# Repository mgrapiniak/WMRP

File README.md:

# Hardware and Arduino Code for DIY WMRP-Solder Station
This is an attempt to implement some improvements:

* Replace LCD with 1.8 Inch Serial SPI TFT LCD Display Module
* Add SPI header onto PCB
* Code amendments

Contributors:
- Bartosz Wapniewski

Video: https://www.youtube.com/watch?v=le2HaKJ6B1A

If you have any questions, please feel free to contact me: flyglas (at) gmail (dot) com

__Features:__
* low offset op amp for soldering tip temperature measurement with type D thermocouple
* cold junction compensation using the PTC (KTY82-110) included in the WMRP soldering pencil
* input voltage measurement (for use with 3 cell lipo battery)
* soldering pencil current measurement 
* recognizing if the soldering pencil rests in the stand (--> standby)
* 3 buttons for save and recall temperature values
* rotary encoder to set soldering temperature
* illuminated 16x2 character LCD module
* USB for debugging and firmware update
* clean and small enclosure
* 4mm safety socket for +12V power input and a protective earth socket for connection to ESD protection

The BOM in the layout folder includes only the parts on the PCB(s).

__Parts (not on PCB):__
* lcd display from ebay "Blue I2C 1602"
* modified connector "Amphenol T 3437 000" (--> http://www.mikrocontroller.net/topic/143288#1500819)
* 4mm safety sockets (red, black, green/yellow) or any other suitable connector
* rotary encoder knob
* display frame "EA027-2UKE"
* aluminium enclosure "Proma 131020"

__Info:__
* close jumper JP1 (activates pullup resistors for I2C wires)
* close jumper JP3 (connection between power ground and analog ground)
* leave jumper JP2 open (alternative for JP3)

__Photos:__

The PCB is a little bit dirty. The Isopropanol was empty and now everything is in the enclosure.

Stand for enclosure Proma 131020:

__First picture of a replica:__

Thank you Dennis for the nice conversation and the picture.

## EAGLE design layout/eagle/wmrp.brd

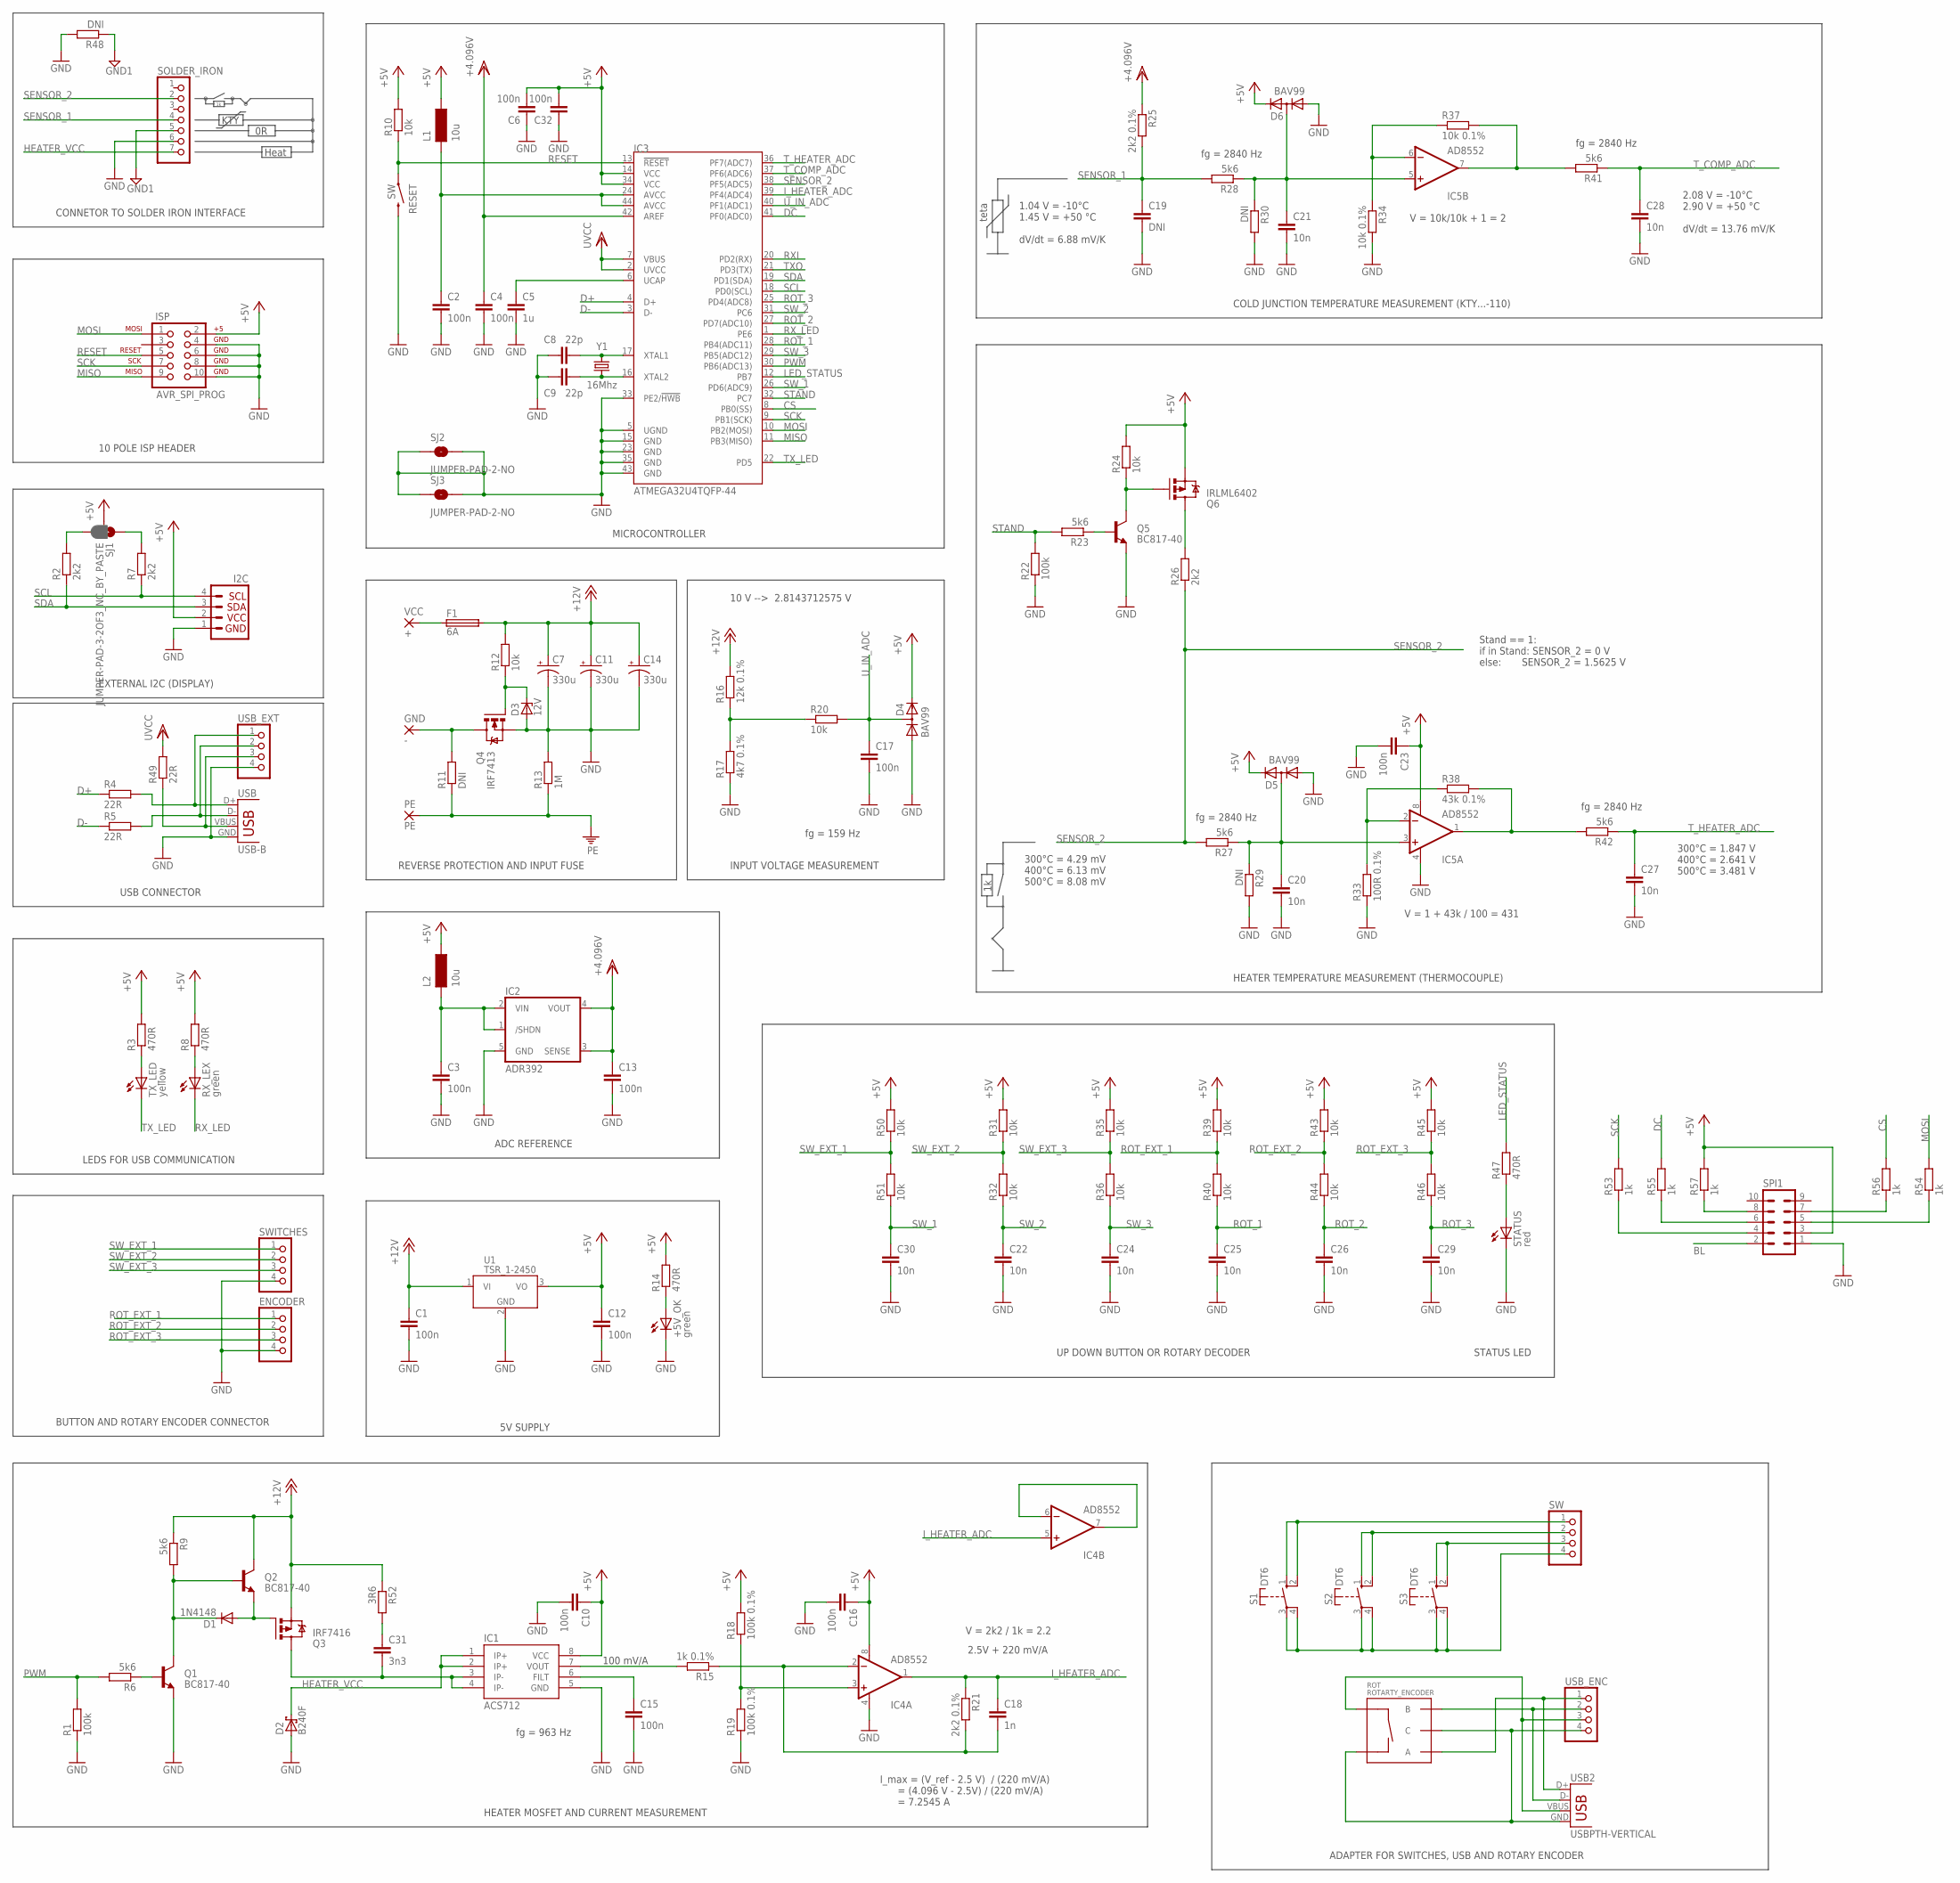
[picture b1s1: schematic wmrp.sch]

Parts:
+5V_OK: green; CHIPLED_1206
C1, C2, C3, C4, C6, C10, C12, C13, C15, C16, C17, C23, C32: 100n; C1206
C5: 1u; C1206
C7, C11, C14: 330u; CPOL-RADIAL-1000UF-25V
C8, C9: 22p; C1206
C18: 1n; C1206
C19: DNI; C1206
C20, C21, C22, C24, C25, C26, C27, C28, C29, C30: 10n; C1206
C31: 3n3; C1206
D1: 1N4148; MINIMELF
D2: B240F; SMB
D3: 12V; SOT23
D4, D5, D6: BAV99; SOT23
ENCODER: PINHD-1X4; 1X04
F1: 6A; SH22,5
GND: -; 2,2
I2C: I2C_STANDARD; 1X04
IC1: ACS712; SO08
IC2: ADR392; SOT23-5
IC3: ATMEGA32U4TQFP-44; TQFP44
IC4, IC5: AD8552; SO08
ISP: AVR_SPI_PROG; AVR_ICSP
L1, L2: 10u; INDUCTOR-1206
PE: PE; 2,2
Q1, Q2, Q5: BC817-40; SOT23-3
Q3: IRF7416; SO-08
Q4: IRF7413; SO-08
Q6: IRLML6402; SOT23-3
R1, R22: 100k; R1206
R2, R7, R26: 2k2; R1206
R3, R8, R14, R47: 470R; R1206
R4, R5, R49: 22R; R1206
R6, R9, R23, R27, R28, R41, R42: 5k6; M1206
R10, R12, R20, R24, R31, R32, R35, R36, R39, R40, R43, R44, R45, R46, R50, R51: 10k; R1206
R11, R48: DNI; R1206
R13: 1M; R1206
R15: 1k 0.1%; M1206
R16: 12k 0.1%; R1206
R17: 4k7 0.1%; R1206
R18, R19: 100k 0.1%; M1206
R21, R25: 2k2 0.1%; M1206
R29, R30: DNI; M1206
R33: 100R 0.1%; M1206
R34, R37: 10k 0.1%; M1206
R38: 43k 0.1%; M1206
R52: 3R6; M1206
R53, R54, R55, R56, R57: 1k; R1206
RESET: SW; TACTILE-PTH
ROT: ROTARTY_ENCODER; ROTARY_ENC_PLAIN
RX_LEX: green; CHIPLED_1206
S1, S2, S3: DT6
SJ1: JUMPER-PAD-3-2OF3_NC_BY_PASTE; PAD-JUMPER-3-2OF3_NC_BY_PASTE_YES_SILK_FULL_BOX
SJ2, SJ3: JUMPER-PAD-2-NO; PAD-JUMPER-2-NO_NO_SILK
SOLDER_IRON: PINHD-1X7; 1X07
SPI1: MA05-2
STATUS: red; CHIPLED_1206
SW: PINHD-1X4; 1X04
SWITCHES: PINHD-1X4; 1X04
TX_LED: yellow; CHIPLED_1206
U1: TSR_1-2450; TSR-1
USB: USB-B; USB-B-PTH
USB2: USBPTH-VERTICAL; USB-B-PTH-VERTICAL
USB_ENC: PINHD-1X4; 1X04
USB_EXT: PINHD-1X4; 1X04
VCC: +; 2,2
Y1: 16Mhz; HC49US

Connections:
+4.096V: C4.1, C13.1, IC2.3 (SENSE), IC2.4 (VOUT), IC3.42 (AREF), R25.1
+5V: C6.2, C10.1, C12.1, C16.1, C23.1, C32.2, D4.2 (C2), D5.2 (C2), D6.2 (C2), I2C.2, IC1.8 (VCC), IC3.14 (VCC), IC3.34 (VCC), IC4.8 (V+), IC5.8 (V+), ISP.2, L1.P$1 (1), L2.P$1 (1), Q6.2 (S), R3.2, R8.2, R10.2, R14.2, R18.2, R24.2, R31.2, R35.2, R39.2, R43.2, R45.2, R50.2, R57.2, SJ1.2, SPI1.3, U1.3 (VO)
+12V: C1.1, C7.1 (+), C11.1 (+), C14.1 (+), F1.2, Q2.3 (C), Q3.1 (S), Q3.2 (S), Q3.3 (S), R9.1, R12.2, R16.2, R52.1, U1.1 (VI)
AVCC: C2.1, IC3.24 (AVCC), IC3.44 (AVCC), L1.P$2 (2)
BL: SPI1.2
CS: IC3.8 (PB0(SS)), R56.2
D+: IC3.4 (D+), R4.1
D-: IC3.3 (D-), R5.1
DC: IC3.41 (PF0(ADC0)), R55.2
GND: +5V_OK.C, C1.2, C2.2, C3.2, C4.2, C5.2, C6.1, C7.2 (-), C8.1, C9.1, C10.2, C11.2 (-), C12.2, C13.2, C14.2 (-), C15.2, C16.2, C17.2, C19.2, C20.2, C21.2, C22.2, C23.2, C24.2, C25.2, C26.2, C27.2, C28.2, C29.2, C30.2, C32.1, D2.A, D3.1 (A), D4.1 (A1), D5.1 (A1), D6.1 (A1), ENCODER.4, I2C.1, IC1.5 (GND), IC2.5 (GND), IC3.5 (UGND), IC3.15 (GND), IC3.23 (GND), IC3.33 (PE2/!HWB), IC3.35 (GND), IC3.43 (GND), IC4.4 (V-), IC5.4 (V-), ISP.4, ISP.6, ISP.8, ISP.10, Q1.2 (E), Q4.1 (S), Q4.2 (S), Q4.3 (S), Q5.2 (E), R1.1, R13.2, R17.1, R19.1, R22.1, R29.2, R30.2, R33.1, R34.2, R48.2, RESET.3 (2), SJ2.1, SJ2.2, SJ3.1, SJ3.2, SOLDER_IRON.6, SPI1.1, STATUS.C, SWITCHES.4, U1.2 (GND), USB.GND, USB_EXT.4
GND1: R48.1, SOLDER_IRON.5
HEATER_VCC: D2.C, IC1.1 (IP+), IC1.2 (IP+), SOLDER_IRON.7
I_HEATER_ADC: C18.1, IC3.39 (PF4(ADC4)), IC4.1 (OUT), IC4.5 (+IN), R21.1
LED_STATUS: IC3.12 (PB7), R47.2
MISO: IC3.11 (PB3(MISO)), ISP.9
MOSI: IC3.10 (PB2(MOSI)), ISP.1, R54.2
unnamed: GND.1, Q4.5 (D), Q4.6 (D), Q4.7 (D), Q4.8 (D), R11.2
unnamed: D3.3 (C), Q4.4 (G), R12.1
unnamed: D1.C, Q1.3 (C), Q2.1 (B), R9.2
unnamed: Q1.1 (B), R6.1
unnamed: F1.1, VCC.1
unnamed: R8.1, RX_LEX.A
unnamed: S1.3, S1.4, S2.3, S2.4, S3.3, S3.4, SW.4
unnamed: S1.1 (S), S1.2 (S), SW.1
unnamed: R4.2, USB.D+, USB_EXT.1
unnamed: R5.2, USB.D-, USB_EXT.2
unnamed: R16.1, R17.2, R20.1
unnamed: S2.1 (S), S2.2 (S), SW.2
unnamed: S3.1 (S), S3.2 (S), SW.3
unnamed: R2.2, SJ1.3
unnamed: Q5.3 (C), Q6.1 (G), R24.1
unnamed: C15.1, IC1.6 (FILT)
unnamed: Q5.1 (B), R23.1
unnamed: IC4.3 (+IN), R18.1, R19.2
unnamed: R3.1, TX_LED.A
unnamed: IC1.7 (VOUT), R15.2
unnamed: C18.2, IC4.2 (-IN), R15.1, R21.2
unnamed: C20.1, D5.3 (C1A2), IC5.3 (+IN), R27.1, R29.1
unnamed: Q6.3 (D), R26.2
unnamed: IC5.2 (-IN), R33.2, R38.1
unnamed: C21.1, D6.3 (C1A2), IC5.5 (+IN), R28.1, R30.1
unnamed: D1.A, Q2.2 (E), Q3.4 (G)
unnamed: IC5.6 (-IN), R34.1, R37.1
unnamed: C31.2, IC1.3 (IP-), IC1.4 (IP-), Q3.5 (D), Q3.6 (D), Q3.7 (D), Q3.8 (D)
unnamed: R7.2, SJ1.1
unnamed: C3.1, IC2.1 (/SHDN), IC2.2 (VIN), L2.P$2 (2)
unnamed: R49.1, USB.VBUS, USB_EXT.3
unnamed: R47.1, STATUS.A
unnamed: +5V_OK.A, R14.1
unnamed: IC4.6 (-IN), IC4.7 (OUT)
unnamed: R53.1, SPI1.4
unnamed: R54.1, SPI1.5
unnamed: R55.1, SPI1.6
unnamed: R56.1, SPI1.7
unnamed: C31.1, R52.2
unnamed: R57.1, SPI1.8
unnamed: IC5.1 (OUT), R38.2, R42.2
unnamed: IC5.7 (OUT), R37.2, R41.2
PE: PE.1, R11.1, R13.1
PWM: IC3.30 (PB6(ADC13)), R1.2, R6.2
RESET: IC3.13 (!RESET), ISP.5, R10.1, RESET.1
ROT_1: C25.1, IC3.28 (PB4(ADC11)), R40.1
ROT_2: C26.1, IC3.27 (PD7(ADC10)), R44.1
ROT_3: C29.1, IC3.25 (PD4(ADC8)), R46.1
ROT_A_D+: ROT.A, USB2.D+, USB_ENC.1
ROT_B_D-: ROT.B, USB2.D-, USB_ENC.2
ROT_C_GND: ROT.C, ROT.SW-, USB2.GND, USB_ENC.4
ROT_EXT_1: ENCODER.1, R39.1, R40.2
ROT_EXT_2: ENCODER.2, R43.1, R44.2
ROT_EXT_3: ENCODER.3, R45.1, R46.2
ROT_SW_VBUS: ROT.SW+, USB2.VBUS, USB_ENC.3
RXI: IC3.20 (PD2(RX))
RX_LED: IC3.1 (PE6), RX_LEX.C
SCK: IC3.9 (PB1(SCK)), ISP.7, R53.2
SCL: I2C.4, IC3.18 (PD0(SCL)), R7.1
SDA: I2C.3, IC3.19 (PD1(SDA)), R2.1
SENSOR_1: C19.1, R25.2, R28.2, SOLDER_IRON.4
SENSOR_2: IC3.38 (PF5(ADC5)), R26.1, R27.2, SOLDER_IRON.2
STAND: IC3.32 (PC7), R22.2, R23.2
SW_1: C30.1, IC3.26 (PD6(ADC9)), R51.1
SW_2: C22.1, IC3.31 (PC6), R32.1
SW_3: C24.1, IC3.29 (PB5(ADC12)), R36.1
SW_EXT_1: R50.1, R51.2, SWITCHES.1
SW_EXT_2: R31.1, R32.2, SWITCHES.2
SW_EXT_3: R35.1, R36.2, SWITCHES.3
TXO: IC3.21 (PD3(TX))
TX_LED: IC3.22 (PD5), TX_LED.C
T_COMP_ADC: C28.1, IC3.37 (PF6(ADC6)), R41.1
T_HEATER_ADC: C27.1, IC3.36 (PF7(ADC7)), R42.1
UCAP: C5.1, IC3.6 (UCAP)
UVCC: IC3.2 (UVCC), IC3.7 (VBUS), R49.2
U_IN_ADC: C17.1, D4.3 (C1A2), IC3.40 (PF1(ADC1)), R20.2
XTAL1: C8.2, IC3.17 (XTAL1), Y1.2
XTAL2: C9.2, IC3.16 (XTAL2), Y1.1

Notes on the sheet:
REVERSE PROTECTION AND INPUT FUSE
CONNETOR TO SOLDER IRON INTERFACE
fg = 159 Hz
ADC REFERENCE
MICROCONTROLLER
LEDS FOR USB COMMUNICATION
USB CONNECTOR
EXTERNAL I2C (DISPLAY)
10 POLE ISP HEADER
HEATER TEMPERATURE MEASUREMENT (THERMOCOUPLE)
COLD JUNCTION TEMPERATURE MEASUREMENT (KTY...-110)
UP DOWN BUTTON OR ROTARY DECODER
100 mV/A
2.5V + 220 mV/A
teta
V = 10k/10k + 1 = 2
V = 1 + 43k / 100 = 431
1.04 V = -10°C 1.45 V = +50 °C dV/dt = 6.88 mV/K
2.08 V = -10°C 2.90 V = +50 °C dV/dt = 13.76 mV/K
V = 2k2 / 1k = 2.2
I_max = (V_ref - 2.5 V) / (220 mV/A) = (4.096 V - 2.5V) / (220 mV/A) = 7.2545 A
300°C = 4.29 mV 400°C = 6.13 mV 500°C = 8.08 mV
HEATER MOSFET AND CURRENT MEASUREMENT
INPUT VOLTAGE MEASUREMENT
STATUS LED
5V SUPPLY
Heat
KTY
fg = 2840 Hz
fg = 963 Hz
300°C = 1.847 V 400°C = 2.641 V 500°C = 3.481 V
BUTTON AND ROTARY ENCODER CONNECTOR
10 V --> 2.8143712575 V
Stand == 1: if in Stand: SENSOR_2 = 0 V else: SENSOR_2 = 1.5625 V
ADAPTER FOR SWITCHES, USB AND ROTARY ENCODER

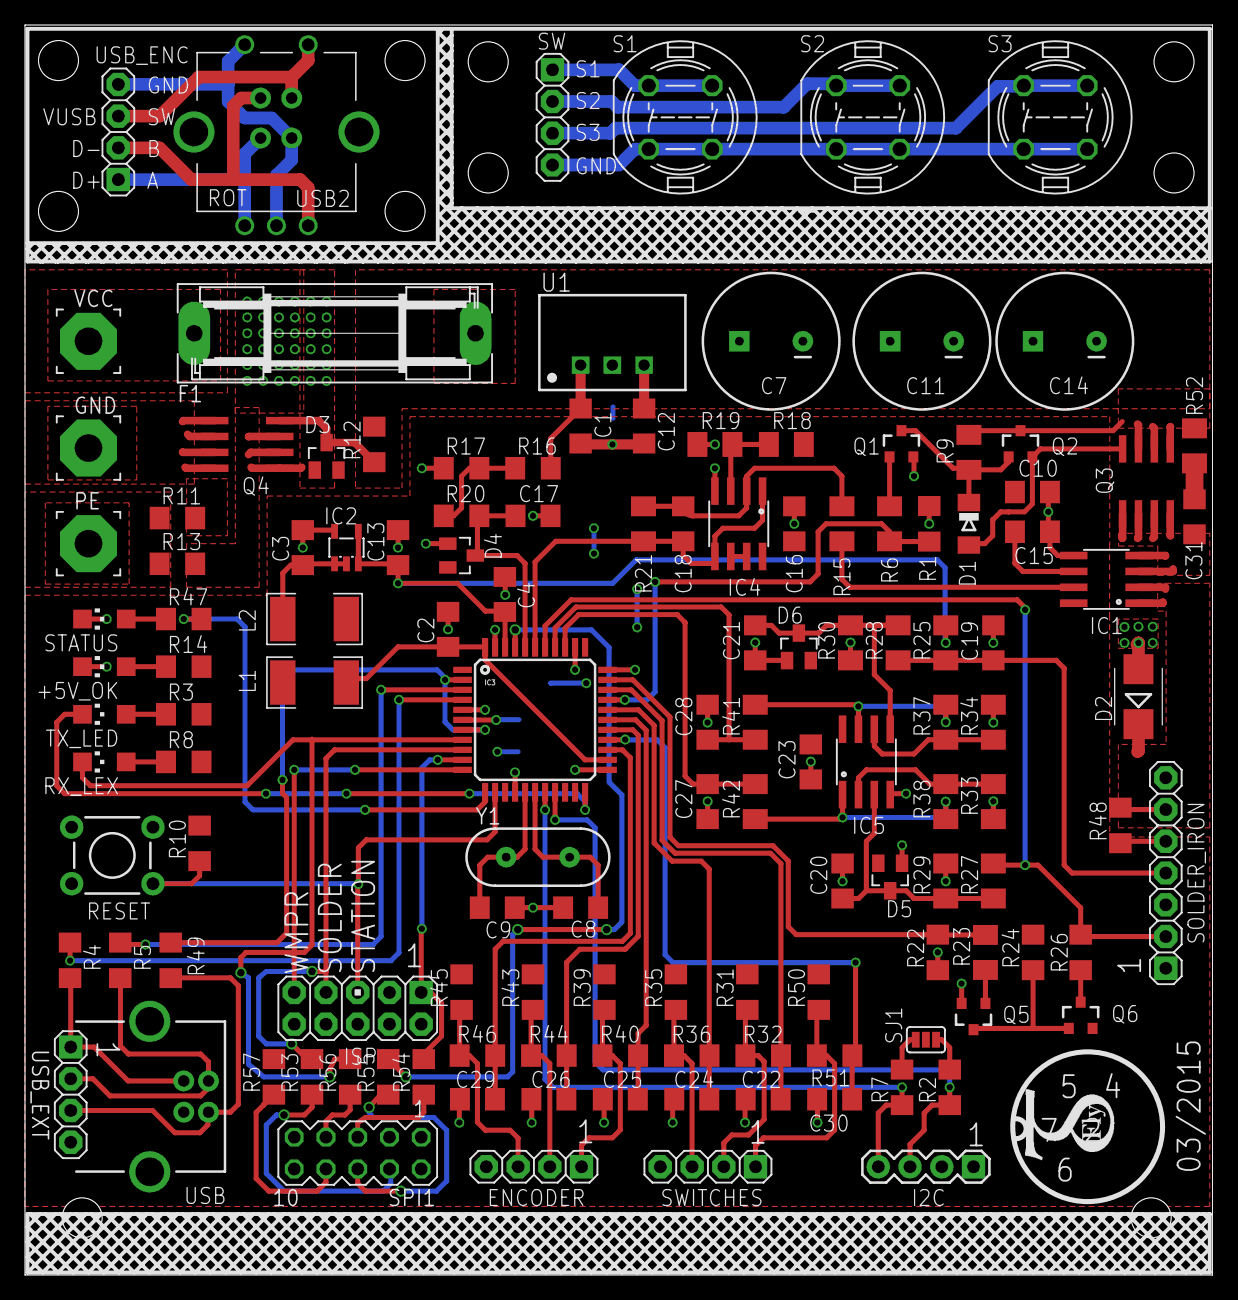
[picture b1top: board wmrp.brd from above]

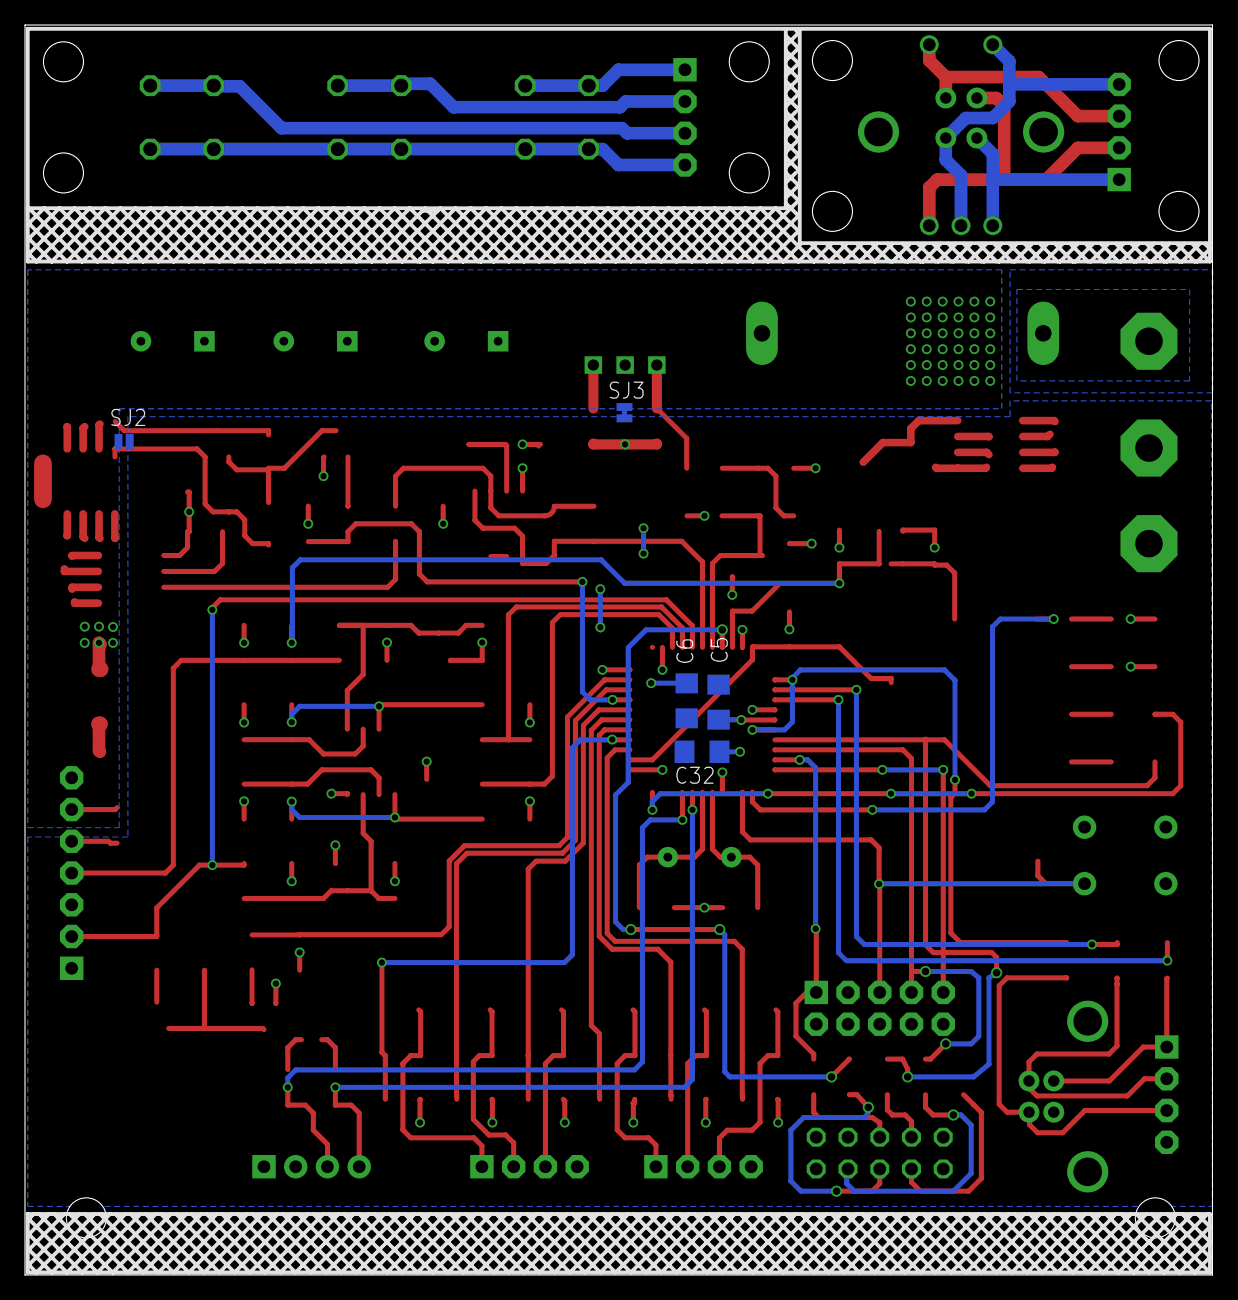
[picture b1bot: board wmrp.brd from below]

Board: 2 copper layers, 95.0 x 100.0 mm, 138 parts (5 on the bottom side), 91 nets.

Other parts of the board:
U$1: LOGO+

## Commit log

2017-02-11 README.md amendments
2017-02-12 .gitignore fix for .brd and .sch files
2017-02-12 testing
2017-02-12 git config settings
2017-02-12 wmrp .brd and .sch unpacked; Eagle temp files added to gitignore
2017-02-12 Added SPI header and resistors to schematic, added SC and BL pin, moved RX_LED from pin 8 to 1
2017-02-15 Added SPI header with resistors to schematic and made connections on PCB
2017-02-15 Modified .gitignore
2017-03-30 Newest updates (DirtyPCB ready)

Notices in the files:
parts and their libraries:
SparkFun-Passives: Licensing: Creative Commons ShareAlike 4.0 International - https://creativecommons.org/licenses/by-sa/4.0
